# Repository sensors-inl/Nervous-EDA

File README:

# Nervous - EDA Sensor

The **Nervous** initiative is a project embracing open-hardware and open-source
principles, with the goal of delivering wearable sensors and accompanying
software for the analysis of Autonomic Nervous System (SNA) activity.

The entire project is published under the MIT Licence.

## Description

This EDA sensor uses continuous multifrequency impedance spectroscopy to measure skin conductivity at 16 simultaneous frequencies with a rate of 8 spectra per second.
The method is fully described detailed in [B. Massot, E. Desmazure, A. Montalibet, E. McAdams and C. Gehin, "A Portable Device Performing Continuous Impedance Spectroscopy for Skin Conductivity," in IEEE Sensors Journal, doi: 10.1109/JSEN.2024.3485187](https://ieeexplore.ieee.org/document/10738317).
The embedded electronic circuit employs two microcontrollers.
The first one is a PSoC Analog co-processor (Infineon) for analog signal generation and conditioning.
The second one is an ISP1807 (Insight SiP) which houses a nRF52840 (Nordic Semiconductor) for voltage and current sampling, impedance calculation and Bluetooth Low Energy communication.

**hardware**: Contained within this folder are ECAD files for the production of PCBs and the assembly of circuits for a wireless, wrist-worn EDA sensor.

**firmware**: This folder contains sources to build binaries for the programming of the two microcontrollers.
Pre-built binaries are also attached to releases of this project.

**software**: While this sensor is primarily intended to be used with the ```nervous-sensors``` Python package included in the Nervous project toolkit, a standalone, web-application is provided for simple usage of the sensor, including sensor control, real-time data visualization and recording.

## Contact

- Author: Bertrand Massot
- Affiliation: INSA Lyon, Ecole Centrale Lyon, Universite Claude Bernard Lyon
1, CPE Lyon, CNRS, INL UMR 5270, 69600 Villeurbanne France.
- Contact email: <bertrand.massot@insa-lyon.fr>

## Funding

This work was supported the French National Reasearch Agency (ANR) under the grant ANR-22-CE31-0023-03 RENFORCE.

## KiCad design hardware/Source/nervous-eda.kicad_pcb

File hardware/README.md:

<p align="center">
    <h1 align="center">Nervous EDA Hardware</h1>
</p>

<p align="center">

</p>

## Table of Contents

- [Table of Contents](#table-of-contents)
- [Overview](#overview)
- [Hardware features](#hardware-features)
- [Manufacturing and assembling](#manufacturing-and-assembling)
  - [PCB properties for manufacturing](#pcb-properties-for-manufacturing)
- [Modification](#modification)
- [Casing](#casing)
- [Note on cables and electrodes placement](#note-on-cables-and-electrodes-placement)
- [Release](#release)

---

## Overview

This folder contains ECAD files for the production of PCBs and assembly of circuits for the Nervous EDA sensor.
The printed circuit board was designed using the open source electronics design automation suite [KiCad EDA](https://www.kicad.org/) v9.0.0

---

## Hardware features

- USB-C connector for charging the battery
- Embedded LiPo battery charger and I2C fuel gauge
- On/Off SPST button (enables/disables the voltage regulator)
- RGB status LED
- CY8C4A45PVI-481 Programmable-System-On-Chip for impedance spectroscopy
- nRF52840 (ISP1807) with Bluetooth Low Energy

---

## Manufacturing and assembling

The following files are available in the `Export` folder:

- **Export/Manufacturing**: contains Gerber (.gbr) and drill files (.drl)
- **Export/Assembly**: contains assembly drawing (.pdf), pick and place files (.pos), and BOM (.csv)

---

### PCB properties for manufacturing

Some PCB manufacturers may require the following properties. The table below summarizes the principal PCB properties:

| Property                    | Value              |
| --------------------------- | ------------------ |
| Dimensions                  | 21.5 mm x 33.5 mm  |
| Number of layers            | 2                  |
| Minimal insulation width    | 0.150 mm           |
| Minimal trace width         | 0.150 mm           |
| Minimal hole size           | 0.200 mm           |

---

## Modification

The `Source` folder contains the original KiCad project, created using KiCad version 7.0.8.

---

## Casing

Several 3D models are available for producing a casing for the electronics. STEP and STL files are located in the `Casing` folder:

- **casing_top** and **casing_bottom** are two parts that assemble together with two M2 screws, where the PCB and a 150 mAh LiPo battery fit. A specially designed battery compartment ensures that it does not overlap with the antenna of the ISAP1807 chip located on the longitudinal edge of the PCB. The design of the bottom part includes handles for wrist attachment.
- **casing_bottom_controller** is a modified version of the bottom part, designed to mount the electronics circuit and battery onto a Valve Index controller for ECG assessment during virtual environment sessions.

---

## Note on cables and electrodes placement

This sensor is designed to capture skin conductivity across two electrodes.
For connectivity, we implemented a simple 2.54 mm, 2-way header on the sensor, allowing for custom electrode connections.
It's advised to use short cables for connecting the two electrodes in proximity to the device.

We recommend using solid-gel electrodes such as Ambu&reg; WhiteSensor 40713 with an initial wear period of 10 minutes before starting measurements.
We constructed cables featuring female crimp terminals on the sensor end and 3 mm banana plugs with a snap adapter on the electrode end.
Finally, securely hold the electrodes in place, along with the cables near the electrodes, using medical tape to minimize noise from connector friction.

---

## Release

The entire folder is provided as an archive (`Nervous-EDA-hardware-vX.X.X.zip`) in the [releases](https://github.com/sensors-inl/Nervous-EDA/releases/latest) of this project.

---

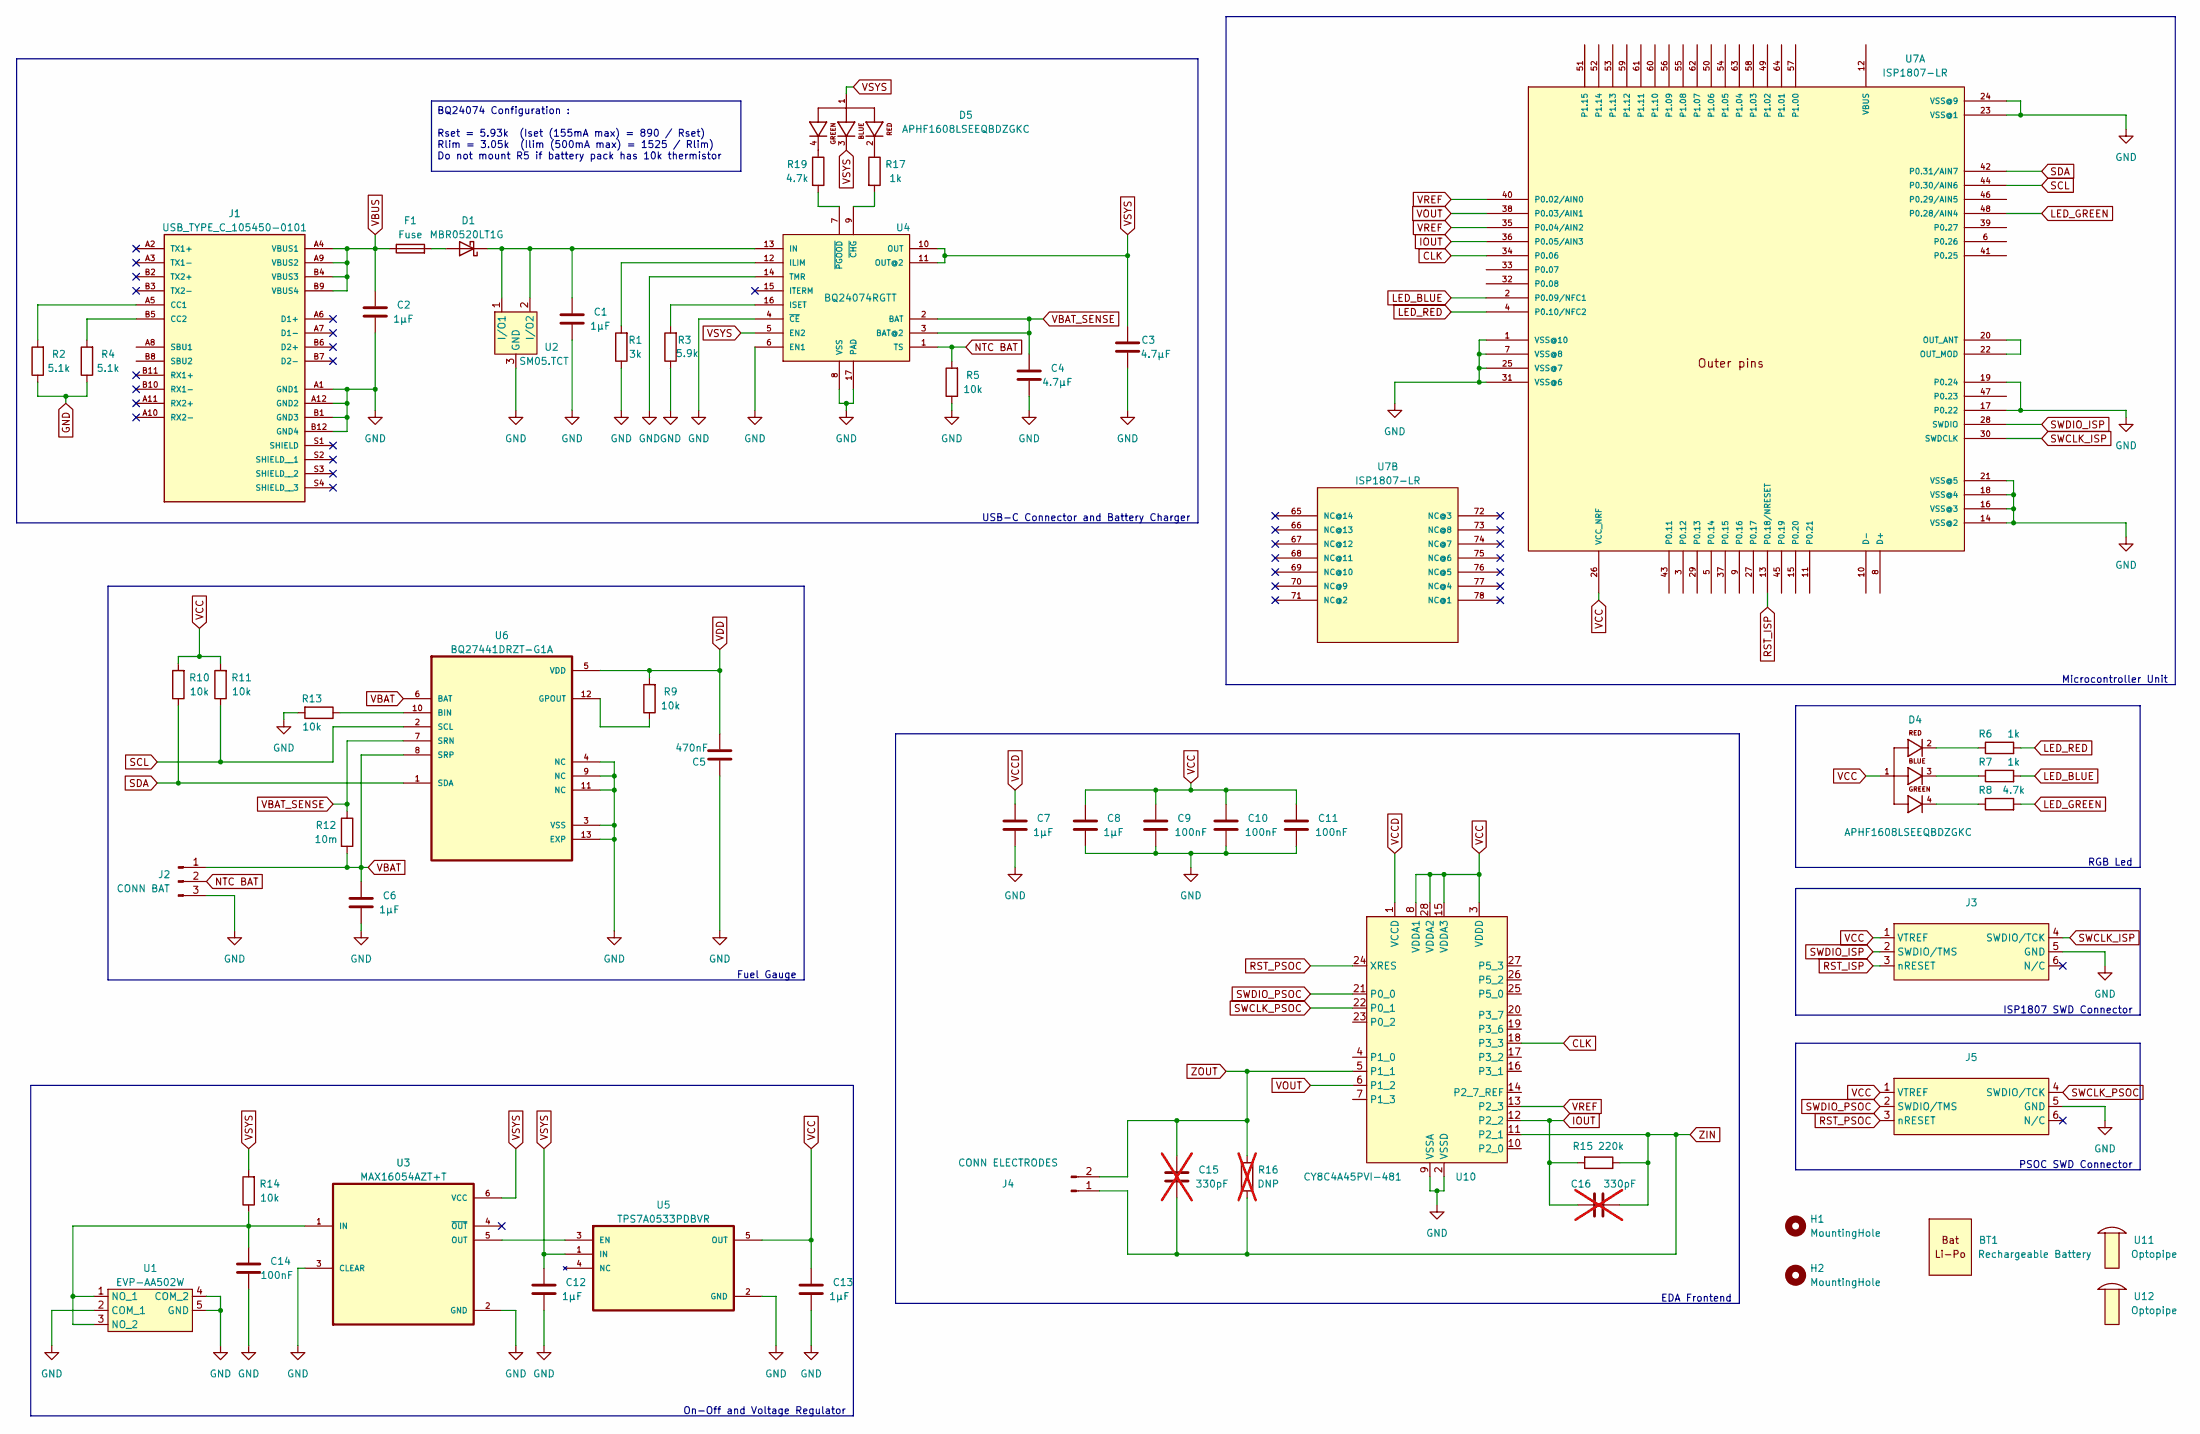
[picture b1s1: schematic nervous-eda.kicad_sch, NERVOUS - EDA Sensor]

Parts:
BT1: BATT LI-PO 3.7V 165MAH; Manufacturer Part Number LP-402025-1S-3
C1, C2, C6, C7, C8, C12, C13: CAP CER 1UF 10V X5R 0402; C_0402_1005Metric; Manufacturer Part Number CC0402KRX5R6BB105
C3, C4: CAP CER 4.7UF 6.3V X5R 0402; C_0402_1005Metric; Manufacturer Part Number CC0402KRX5R5BB475
C5: CAP CER 0.47UF 10V X5R 0402; C_0402_1005Metric; Manufacturer Part Number CC0402KRX5R6BB474
C9, C10, C11, C14: CAP CER 0.1UF 16V X7R 0402; C_0402_1005Metric; Manufacturer Part Number CC0402JRX7R7BB104
C15, C16: CAP CER 330pF 50V C0G / NP0 0805 MCMT; C_0805_2012Metric; Manufacturer Part Number MCMT21N331F500CT; not fitted
D1: DIODE SCHOTTKY 20V 500MA SOD123; D_SOD-123; Manufacturer Part Number STPS0520Z
D4, D5: LED RGB CLEAR 4SMD; APHF1608LSEEQBDZGKC; Manufacturer Part Number APHF1608LSEEQBDZGKC
F1: PTC RESET FUSE 16V 500MA 1210; Fuse_1210_3225Metric; Manufacturer Part Number 0ZCH0050FF2G
H1, H2: MountingHole; MountingHole_2mm
J1: CONN RCP USB3.1 TYPEC 24P SMD RA; USB_TYPE_C_105450-0101; Manufacturer Part Number 105450-0101
J2: MOLEX 53048-0310; CONN_BAT_53048-0310; Manufacturer Part Number 53048-0310
J3, J5: TC2030-MCP-NL
J4: CONN HEADER R/A 4POS 2.54MM; PinHeader_1x02_P2.54mm_Horizontal; Manufacturer Part Number 77315-118-04LF
R1: RES SMD 3K OHM 1% 1/16W 0402; R_0402_1005Metric; Manufacturer Part Number AC0402FR-073KL
R2, R4: RES 5.1K OHM 0.5% 1/10W 0402; R_0402_1005Metric; Manufacturer Part Number ERJ-U2RD5101X
R3: RES 5.9K OHM 1% 1/16W 0402; R_0402_1005Metric; Manufacturer Part Number RC0402FR-075K9L
R5, R9, R10, R11, R13, R14: RES 10K OHM 1% 1/16W 0402; R_0402_1005Metric; Manufacturer Part Number RC0402FR-0710KL
R6, R7, R17: RES 1K OHM 1% 1/16W 0402; R_0402_1005Metric; Manufacturer Part Number RC0402FR-071KL
R8, R19: RES 4.7K OHM 1% 1/16W 0402; R_0402_1005Metric; Manufacturer Part Number RC0402FR-074K7L
R12: RES 0.01 OHM 1% 1/10W 0603; R_0603_1608Metric; Manufacturer Part Number RL0603FR-070R01L
R15: RES Thick Film, 220kΩ, 1%, 0.125W, 100ppm/°C, 0805; R_0805_2012Metric; Manufacturer Part Number RC0805FR-07220KL
R16: RES Thick Film, 220kΩ, 1%, 0.125W, 100ppm/°C, 0805; R_0805_2012Metric; Manufacturer Part Number RC0805FR-07220KL; not fitted
U1: SWITCH TACTILE SPST-NO 0.02A 15V; EVP-AA502W; Manufacturer Part Number EVP-AA502W
U2: TVS Diode WE-TVS-Standard, VRWM=5.0V; SM05.TCT; Manufacturer Part Number SM05.TCT
U3: IC INTFACE SPECIALIZED TSOT23-6; MAX16054AZT+T; Manufacturer Part Number MAX16054AZT+T
U4: IC BATT CHG LI-ION 1CELL 16QFN; BQ24074RGTx; Manufacturer Part Number BQ24074RGTT
U5: IC REG LINEAR 3.3V 200MA SOT23-5; TPS7A0533PDBVR; Manufacturer Part Number TPS7A0533PDBVR
U6: IC BATT FUEL GAUGE LICOO2 12SON; BQ27441DRZR-G1A; Manufacturer Part Number BQ27441DRZR-G1A
U7: RF TXRX MODULE BT TRACE ANT SMD; ISP1807-LR; Manufacturer Part Number ISP1807-LR-RS
U10: IC MCU 32BIT 32KB FLASH 28SSOP; CY8C4A45PVI-481; Manufacturer Part Number CY8C4A45PVI-481
U11, U12: LIGHTPIPE PNL MT CONVEX 0.250"; Manufacturer Part Number 515-1302-0250F

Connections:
CLK: U7.34 (P0.06), U10.18 (P3_3)
GND: C1.2, C2.2, C3.1, C4.2, C5.2, C6.2, C7.2, C8.2, C9.2, C10.2, C11.2, C12.2, C13.2, C14.2, J1.A1 (GND1), J1.A12 (GND2), J1.B1 (GND3), J1.B12 (GND4), J2.3, J3.5 (GND), J5.5 (GND), R1.1, R2.1, R3.1, R4.1, R5.1, R13.2, U1.2 (COM_1), U1.4 (COM_2), U1.5 (GND), U2.3 (GND), U3.2 (GND), U3.3 (CLEAR), U4.4 (~CE), U4.6 (EN1), U4.8 (VSS), U4.14 (TMR), U4.17 (PAD), U5.2 (GND), U6.3 (VSS), U6.4 (NC), U6.9 (NC), U6.11 (NC), U6.13 (EXP), U7.1 (VSS@10), U7.7 (VSS@8), U7.14 (VSS@2), U7.16 (VSS@3), U7.17 (P0.22), U7.18 (VSS@4), U7.19 (P0.24), U7.21 (VSS@5), U7.23 (VSS@1), U7.24 (VSS@9), U7.25 (VSS@7), U7.31 (VSS@6), U10.2 (VSSD), U10.9 (VSSA)
IOUT: C16.1, R15.2, U7.36 (P0.05/AIN3), U10.12 (P2_2)
LED_BLUE: R7.2, U7.2 (P0.09/NFC1)
LED_GREEN: R8.2, U7.48 (P0.28/AIN4)
LED_RED: R6.2, U7.4 (P0.10/NFC2)
NTC BAT: J2.2, R5.2, U4.1 (TS)
unnamed: D1.2 (A), F1.2
unnamed: C1.1, D1.1 (K), U2.1 (I/O1), U2.2 (I/O2), U4.13 (IN)
unnamed: D4.2, R6.1
unnamed: D4.3, R7.1
unnamed: D4.4, R8.1
unnamed: D5.2, R17.1
unnamed: D5.4, R19.1
unnamed: J1.A5 (CC1), R2.2
unnamed: J1.B5 (CC2), R4.2
unnamed: C14.1, R14.1, U1.1 (NO_1), U1.3 (NO_2), U3.1 (IN)
unnamed: U3.5 (OUT), U5.3 (EN)
unnamed: R1.2, U4.12 (ILIM)
unnamed: R3.2, U4.16 (ISET)
unnamed: R17.2, U4.9 (~CHG)
unnamed: R19.2, U4.7 (~PGOOD)
unnamed: R13.1, U6.10 (BIN)
unnamed: R9.1, U6.12 (GPOUT)
unnamed: U7.20 (OUT_ANT), U7.22 (OUT_MOD)
RST_ISP: J3.3 (nRESET), U7.13 (P0.18/NRESET)
RST_PSOC: J5.3 (nRESET), U10.24 (XRES)
SCL: R11.1, U6.2 (SCL), U7.44 (P0.30/AIN6)
SDA: R10.1, U6.1 (SDA), U7.42 (P0.31/AIN7)
SWCLK_ISP: J3.4 (SWDIO/TCK), U7.30 (SWDCLK)
SWCLK_PSOC: J5.4 (SWDIO/TCK), U10.22 (P0_1)
SWDIO_ISP: J3.2 (SWDIO/TMS), U7.28 (SWDIO)
SWDIO_PSOC: J5.2 (SWDIO/TMS), U10.21 (P0_0)
VBAT: C6.1, J2.1, R12.2, U6.6 (BAT), U6.8 (SRP)
VBAT_SENSE: C4.1, R12.1, U4.2 (BAT), U4.3 (BAT@2), U6.7 (SRN)
VBUS: C2.1, F1.1, J1.A4 (VBUS1), J1.A9 (VBUS2), J1.B4 (VBUS3), J1.B9 (VBUS4)
VCC: C8.1, C9.1, C10.1, C11.1, C13.1, D4.1, J3.1 (VTREF), J5.1 (VTREF), R10.2, R11.2, U5.5 (OUT), U7.26 (VCC_NRF), U10.3 (VDDD), U10.8 (VDDA1), U10.15 (VDDA3), U10.28 (VDDA2)
VCCD: C7.1, U10.1 (VCCD)
VDD: C5.1, R9.2, U6.5 (VDD)
VOUT: U7.38 (P0.03/AIN1), U10.6 (P1_2)
VREF: U7.35 (P0.04/AIN2), U7.40 (P0.02/AIN0), U10.13 (P2_3)
VSYS: C3.2, C12.1, D5.1, D5.3, R14.2, U3.6 (VCC), U4.5 (EN2), U4.10 (OUT), U4.11 (OUT@2), U5.1 (IN)
ZIN: C15.2, C16.2, J4.1, R15.1, R16.1, U10.11 (P2_1)
ZOUT: C15.1, J4.2, R16.2, U10.5 (P1_1)

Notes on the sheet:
Fuel Gauge
On-Off and Voltage Regulator
RGB Led
ISP1807 SWD Connector
Microcontroller Unit
EDA Frontend
PSOC SWD Connector
USB-C Connector and Battery Charger
BQ24074 Configuration : Rset = 5.93k (Iset (155mA max) = 890 / Rset) Rlim = 3.05k (Ilim (500mA max) = 1525 / Rlim) Do not mount R5 if battery pack has 10k thermistor

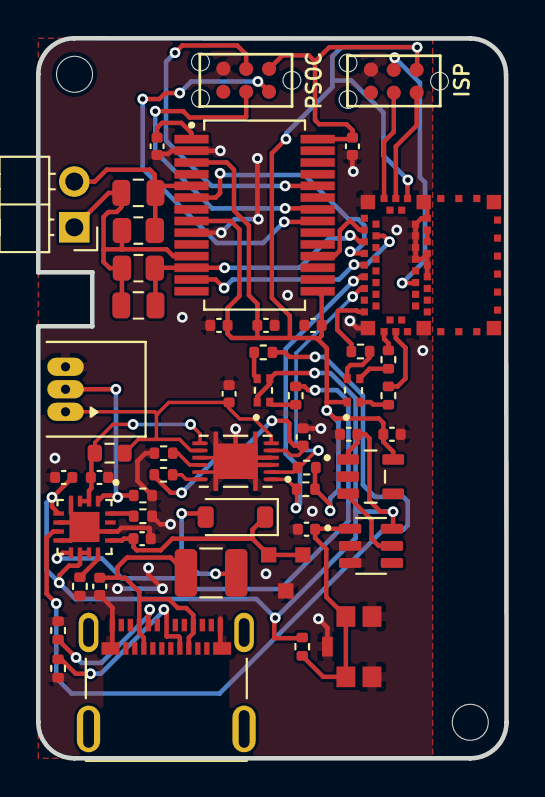
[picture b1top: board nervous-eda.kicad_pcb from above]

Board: 2 copper layers, 26.0 x 40.0 mm, 53 parts (0 on the bottom side), 44 nets.

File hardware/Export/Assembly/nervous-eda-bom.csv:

Reference;Value;Qty;Manufacturer;Manufacturer Part Number;Supplier;Supplier Part Number
BT1;BATT LI-PO 3.7V 165MAH;1;BAK TECHNOLOGY;LP-402025-1S-3;FARNELL;2077885
C1,C2,C6,C7,C8,C12,C13;CAP CER 1UF 10V X5R 0402;7;Yageo;CC0402KRX5R6BB105;Farnell;1458896
C3,C4;CAP CER 4.7UF 6.3V X5R 0402;2;Yageo;CC0402KRX5R5BB475;Farnell;3369135
C5;CAP CER 0.47UF 10V X5R 0402;1;Yageo;CC0402KRX5R6BB474;Farnell;3369138
C9,C10,C11,C14;CAP CER 0.1UF 16V X7R 0402;4;Yageo;CC0402JRX7R7BB104;Farnell;3369125
D1;DIODE SCHOTTKY 20V 500MA SOD123;1;STMicroelectronics;STPS0520Z;FARNELL;1467545
D4,D5;LED RGB CLEAR 4SMD;2;KINGBRIGHT;APHF1608LSEEQBDZGKC;DIGIKEY;754-2143-1-ND
F1;PTC RESET FUSE 16V 500MA 1210;1;BEL;0ZCH0050FF2G;Farnell;2848519
J1;CONN RCP USB3.1 TYPEC 24P SMD RA;1;MOLEX;105450-0101;FARNELL;2524076
J2;MOLEX 53048-0310;1;MOLEX;53048-0310;FARNELL;9732918
J4;CONN HEADER R/A 4POS 2.54MM;1;AMPHENOL COMMUNICATIONS SOLUTIONS;77315-118-04LF;FARNELL;3728851
R1;RES SMD 3K OHM 1% 1/16W 0402;1;Yageo;AC0402FR-073KL;Farnell;3951323
R2,R4;RES 5.1K OHM 0.5% 1/10W 0402;2;PANASONIC;ERJ-U2RD5101X;FARNELL;3516311
R3;RES 5.9K OHM 1% 1/16W 0402;1;Yageo;RC0402FR-075K9L;Farnell;3951010
R5,R9,R10,R11,R13,R14;RES 10K OHM 1% 1/16W 0402;6;Yageo;RC0402FR-0710KL;Farnell;9239359
R6,R7,R17;RES 1K OHM 1% 1/16W 0402;3;Yageo;RC0402FR-071KL;Farnell;9239235
R8,R19;RES 4.7K OHM 1% 1/16W 0402;2;Yageo;RC0402FR-074K7L;Farnell;9239316
R12;RES 0.01 OHM 1% 1/10W 0603;1;Yageo;RL0603FR-070R01L;Farnell;8067767
R15;RES Thick Film, 220kΩ, 1%, 0.125W, 100ppm/°C, 0805;1;Yageo;RC0805FR-07220KL;Mouser;603-RC0805FR-07220KL
U1;SWITCH TACTILE SPST-NO 0.02A 15V;1;PANASONIC;EVP-AA502W;FARNELL;2831733
U2;TVS Diode WE-TVS-Standard, VRWM=5.0V;1;SEMTECH;SM05.TCT;Farnell;1456392
U3;IC INTFACE SPECIALIZED TSOT23-6;1;ANALOG DEVICES;MAX16054AZT+T;FARNELL;2515822
U4;IC BATT CHG LI-ION 1CELL 16QFN;1;TEXAS INSTRUMENTS;BQ24074RGTT;FARNELL;3123775
U5;IC REG LINEAR 3.3V 200MA SOT23-5;1;TEXAS INSTRUMENTS;TPS7A0533PDBVR;DIGIKEY;296-TPS7A0533PDBVRDKR-ND
U6;IC BATT FUEL GAUGE LICOO2 12SON;1;TEXAS INSTRUMENTS;BQ27441DRZR-G1A;FARNELL;3123775
U7;RF TXRX MODULE BT TRACE ANT SMD;1;INSIGHT SIP;ISP1807-LR-RS;DIGIKEY;1786-1019-1-ND
U10;IC MCU 32BIT 32KB FLASH 28SSOP;1;Infineon;CY8C4A45PVI-481;Digi-Key;448-CY8C4A45PVI-481-ND
U11,U12;LIGHTPIPE PNL MT CONVEX 0.250";2;DIALIGHT;515-1302-0250F;FARNELL;3775816

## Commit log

2024-11-25 feat: add build in CI for firmwares and create release files
2024-11-25 doc: improve documentation
2025-02-15 feat: use RTC clock for sampling instead of HFClk for precision
2025-02-15 fix: apply phase correction based on 100us ADC/DAC delay
2025-02-15 chore: update generated files
2025-02-15 fix: bump libncurses version for latest ubuntu
2025-02-15 doc: document change log for this version
2025-02-17 chore: cosmetics
2025-03-20 fix : readjustment of decoupling capacity positioning
2025-03-20 feat: bump to KiCad 9.0.0
2025-03-20 fix: export files
2025-03-21 fix: add device name in csv file
2025-04-04 feat: add second history chart for 724 Hz
2025-09-17 fix: [hw] 3D body path for components
2025-10-01 fix: [hw] cosmetics, export files and version update
2025-10-01 chore: changelog

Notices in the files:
hardware/README.md:
License: MIT
hardware/Source/nervous-eda.kicad_pcb:
Copyright (c) 2024 INSA Lyon, CNRS, INL UMR5270
License : MIT License
